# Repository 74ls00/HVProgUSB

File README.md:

# HVProgUSB

Параллельный программатор AVR на базе STK500. Вход на PL2303, для прошивки программатор не требуется

Инструкция по настройке https://74ls00.github.io/hwprog/help.html

2018.10 добавлен светодиод 3.3в PL2303

Фото моего прибора в папке /pic

Вариант в dip корпусе планировался как тестовый, но заброшен

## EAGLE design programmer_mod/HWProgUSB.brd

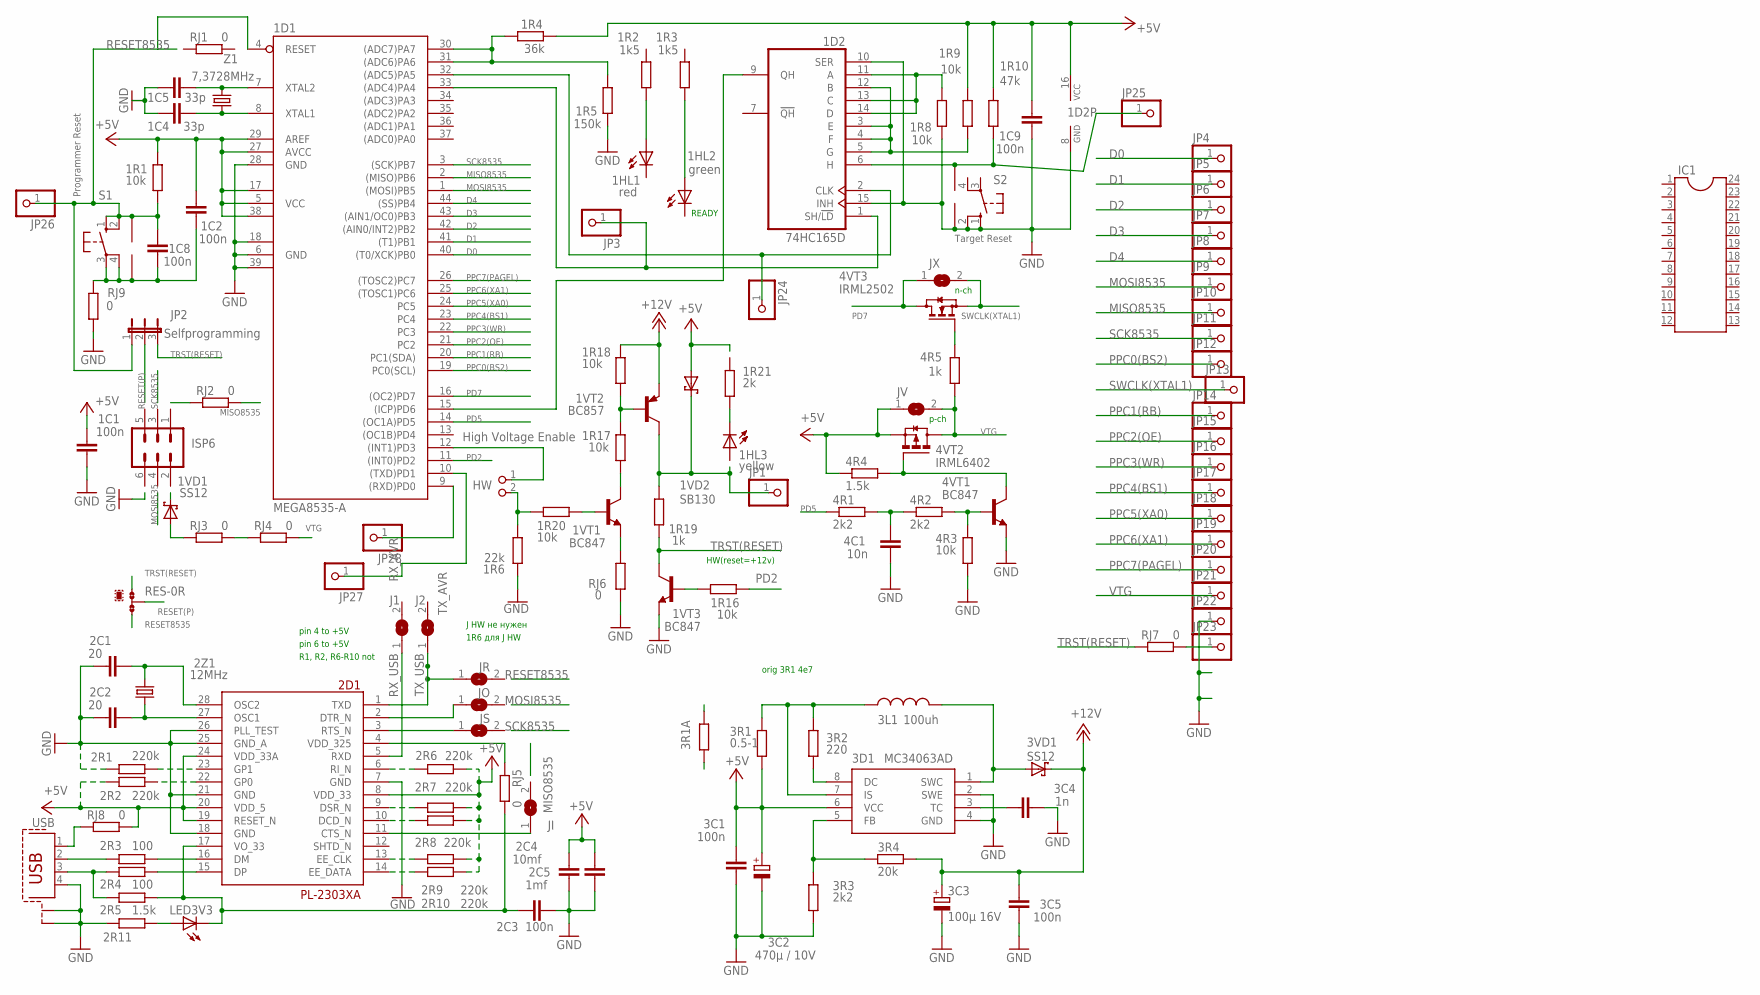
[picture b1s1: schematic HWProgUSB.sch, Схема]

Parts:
1C1, 1C2, 1C8, 1C9, 2C3: 100n; C0805
1C4, 1C5: 33p; C0805
1D1: MEGA8535-A; TQFP44
1D2: 74HC165D; SO16
1HL1: red; LED5MM
1HL2: green; LED5MM
1HL3: yellow; LED5MM
1R1, 1R8, 1R9, 1R17, 1R18, 1R20, 4R3: 10k; M0805
1R2, 1R3: 1k5; M0805
1R4: 36k; M0805
1R5: 150k; R1206
1R6: 22k; M1206
1R10: 47k; M0805
1R16: 10k; R0805
1R19, 4R5: 1k; M0805
1R21: 2k; R1206W
1VD1, 3VD1: SS12; SMB
1VD2: SB130; SMB
1VT1, 1VT3, 4VT1: BC847; SOT23
1VT2: BC857; SOT23-BEC
2C1, 2C2: 20; C0805
2C4: 10mf; C1210
2C5: 1mf; C0805
2D1: PL-2303XA; SSOP28DB
2R1, 2R7, 2R8, 2R9, 2R10: 220k; R0603
2R2, 2R6: 220k; R1206W
2R3, 2R4: 100; R0603
2R5: 1.5k; R0603
2R11: R-EU_R0603; R0603
2Z1: 12MHz; HC49/S
3C1: 100n; C025-024X044
3C2: 470µ / 10V; RCL_E3,5-8
3C3: 100µ 16V; RCL_E3,5-8
3C4: 1n; C025-025X050
3C5: 100n; C025-025X050
3D1: MC34063AD; SOIC8
3L1: 100uh; 0207/10
3R1: 0.5-1; 0204/7
3R1A: R-EU_0204/7; 0204/7
3R2: 220; 0204/7
3R3, 4R1: 2k2; M0805
3R4: 20k; M0805
4C1: 10n; C1206
4R2: 2k2; M1206
4R4: 1.5k; M0805
4VT2: IRML6402; SUPER-SOT3
4VT3: IRML2502; SOT23
HW: High Voltage Enable; PINHEAD_1X02
IC1: DIL24-9
ISP6: MA03-2
J1, J2: SJ
JI: SJ
JO: SJ
JP1, JP3, JP4, JP5, JP6, JP7, JP8, JP9, JP10, JP11, JP12, JP13, JP14, JP15, JP16, JP17, JP18, JP19, JP20, JP21, JP22, JP23, JP24, JP25, JP26, JP27, JP28: PINHD-1X1; 1X01
JP2: Selfprogramming; JUMPER_JP2
JR: SJ
JS: SJ
JV: SJ
JX: SJ
LED3V3: LEDCHIPLED_0603; CHIPLED_0603
RES: 0R-JUMPA; A0R-JMP
RJ1, RJ2, RJ3, RJ4, RJ5, RJ6, RJ7, RJ8, RJ9: 0; R1206
S1, S2: 10-XX; B3F-10XX
U$1, U$2: 5.08; KEY
USB: PROGRAMMER_PN61729-S
Z1: 7,3728MHz; HC49U-V

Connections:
3VUSB: 2C3.1, 2D1.17 (VO_33), 2R5.1, LED3V3.C, RJ5.2
+5V: 1C1.2, 1C2.2, 1C9.1, 1D1.5 (VCC), 1D1.17 (VCC1), 1D1.27 (AVCC), 1D1.29 (AREF), 1D1.38 (VCC2), 1D2.16 (VCC), 1R1.2, 1R4.2, 1R9.1, 1R10.1, 1VD2.A, 2C4.2, 2C5.2, 2D1.8 (VDD_33), 2D1.19 (RESET_N), 2D1.20 (VDD_5), 2D1.24 (VDD_33A), 2R2.1, 2R6.2, 2R7.1, 2R8.1, 2R9.1, 2R10.1, 3C1.1, 3C2.+, 3D1.6 (VCC), 3R1.1, 3R1A.1, 4R4.1, 4VT2.2 (S), JV.1, RJ8.2
+12V: 1R18.2, 1VT2.E, 3C3.+, 3C5.2, 3R4.2, 3VD1.C
D0: 1D1.40 ((T0/XCK)PB0), JP4.1
D1: 1D1.41 ((T1)PB1), JP5.1
D2: 1D1.42 ((AIN0/INT2)PB2), JP6.1
D3: 1D1.43 ((AIN1/OC0)PB3), JP7.1
D4: 1D1.44 ((SS)PB4), JP8.1
GND: 1C1.1, 1C4.1, 1C5.1, 1C9.2, 1D1.6 (GND), 1D1.18 (GND1), 1D1.28 (GND), 1D1.39 (GND2), 1D2.8 (GND), 1D2.10 (SER), 1D2.15 (INH), 1R5.1, 1R6.1, 1R8.1, 1VT3.2 (E), 2C1.1, 2C2.1, 2C3.2, 2C4.1, 2C5.1, 2D1.7 (GND), 2D1.18 (GND), 2D1.21 (GND), 2D1.25 (GND_A), 2D1.26 (PLL_TEST), 2R1.1, 2R11.2, 3C1.2, 3C2.-, 3C3.-, 3C4.2, 3C5.1, 3D1.2 (SWE), 3D1.4 (GND), 3R3.1, 4C1.1, 4R3.1, 4VT1.2 (E), JP22.1, RJ6.1, RJ9.1, S2.1 (S), S2.2 (S1), U$2.P$1, USB.4, USB.S1, USB.S2
MISO8535: 1D1.2 ((MISO)PB6), JP10.1, RJ2.2
MOSI8535: 1D1.1 ((MOSI)PB5), JP9.1
N4: 1D1.33 ((ADC4)PA4), 1D2.1 (SH/!LD), JP3.1
unnamed: JP23.1, RJ7.2
unnamed: 2D1.4 (VDD_325), RJ5.1
unnamed: 1VT1.2 (E), RJ6.2
unnamed: 2D1.9 (DSR_N), 2R7.2
unnamed: 1VD1.A, RJ3.1
unnamed: RJ3.2, RJ4.1
unnamed: 1C5.2, 1D1.7 (XTAL2), Z1.2
unnamed: 1C4.2, 1D1.8 (XTAL1), Z1.1
unnamed: RJ8.1, USB.1
unnamed: 1C2.1, 1C8.1, RJ9.2, S1.3, S1.4 (P1), U$1.P$1
unnamed: 1HL3.K (C), 1R21.1
unnamed: 4R5.2, 4VT3.1 (G)
unnamed: 2R11.1, LED3V3.A
unnamed: 2R4.1, 2R5.2, USB.3
unnamed: 2R3.1, USB.2
unnamed: 2D1.15 (DP), 2R4.2
unnamed: 2D1.16 (DM), 2R3.2
unnamed: 2D1.23 (GP1), 2R1.2
unnamed: 2D1.22 (GP0), 2R2.2
unnamed: 2C1.2, 2D1.28 (OSC2), 2Z1.2
unnamed: 2D1.11 (CTS_N), JI.1
unnamed: 4R2.2, 4R3.2, 4VT1.1 (B)
unnamed: 2C2.2, 2D1.27 (OSC1), 2Z1.1
unnamed: 2D1.6 (RI_N), 2R6.1
unnamed: 4R4.2, 4VT1.3 (C), 4VT2.1 (G)
unnamed: 2D1.3 (RTS_N), JS.1
unnamed: 4C1.2, 4R1.2, 4R2.1
unnamed: 2D1.13 (EE_CLK), 2R9.2
unnamed: 2D1.2 (DTR_N), JO.1
unnamed: 2D1.14 (EE_DATA), 2R10.2
unnamed: 2D1.10 (DCD_N), 2R8.2
unnamed: 3D1.8 (DC), 3R2.1
unnamed: 3D1.7 (IS), 3L1.1, 3R1.2, 3R1A.2, 3R2.2
unnamed: 3D1.5 (FB), 3R3.2, 3R4.1
unnamed: 3D1.1 (SWC), 3L1.2, 3VD1.A
unnamed: 3C4.1, 3D1.3 (TC)
unnamed: 1HL2.A, 1R3.1
unnamed: 1D1.30 ((ADC7)PA7), 1D1.31 ((ADC6)PA6), 1R4.1, 1R5.2
unnamed: 1D1.32 ((ADC5)PA5), 1D2.2 (CLK), JP24.1
unnamed: 1D2.6 (H), 1R10.2, JP25.1, U$2.P$2
unnamed: 1D1.12 ((INT1)PD3), HW.1
unnamed: 1R6.2, 1R20.2, HW.2
unnamed: 1R19.2, 1VD2.C, 1VT2.C, JP1.1
unnamed: 1R20.1, 1VT1.1 (B)
unnamed: 1R17.1, 1VT1.3 (C)
unnamed: 1R17.2, 1R18.1, 1VT2.B
unnamed: 1D1.15 ((ICP)PD6), 1D2.9 (QH)
unnamed: 1HL1.A, 1R2.1
unnamed: 1D2.11 (A), 1D2.13 (C), 1D2.14 (D), 1R8.2
unnamed: 1D2.3 (E), 1D2.4 (F), 1D2.5 (G), 1D2.12 (B), 1R9.2
unnamed: 1R16.2, 1VT3.1 (B)
PD2: 1D1.11 ((INT0)PD2), 1R16.1
PD5: 1D1.14 ((OC1A)PD5), 4R1.1
PD7: 1D1.16 ((OC2)PD7), 4VT3.3 (D), JX.1
PPC0(BS2): 1D1.19 (PC0(SCL)), JP12.1
PPC1(RB): 1D1.20 (PC1(SDA)), JP14.1
PPC2(OE): 1D1.21 (PC2), JP15.1
PPC3(WR): 1D1.22 (PC3), JP16.1
PPC4(BS1): 1D1.23 (PC4), JP17.1
PPC5(XA0): 1D1.24 (PC5), JP18.1
PPC6(XA1): 1D1.25 ((TOSC1)PC6), JP19.1
PPC7(PAGEL): 1D1.26 ((TOSC2)PC7), JP20.1
RESET8535: 1C8.2, 1D1.4 (RESET), 1R1.1, JP2.1, JP26.1, RES.3, S1.1 (S), S1.2 (S1), U$1.P$2
RESET(P): JP2.2, RES.2
RX_AVR: 1D1.10 ((TXD)PD1), JP27.1
RX_USB: 2D1.5 (RXD), J1.1
SCK8535: 1D1.3 ((SCK)PB7), JP11.1
SWCLK(XTAL1): 4VT3.2 (S), JP13.1, JX.2
TRST(RESET): 1R19.1, 1VT3.3 (C), JP2.3, RES.1, RJ7.1
TX_AVR: 1D1.9 ((RXD)PD0), JP28.1
TX_USB: 2D1.1 (TXD), J2.1, JR.1
VTG: 4R5.1, 4VT2.3 (D), JP21.1, JV.2, RJ4.2

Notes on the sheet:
Target Reset
Programmer Reset
pin 4 to +5V
R1, R2, R6-R10 not
pin 6 to +5V
orig 3R1 4e7
J HW не нужен
1R6 для J HW
HW(reset=+12v)
READY
n-ch
p-ch

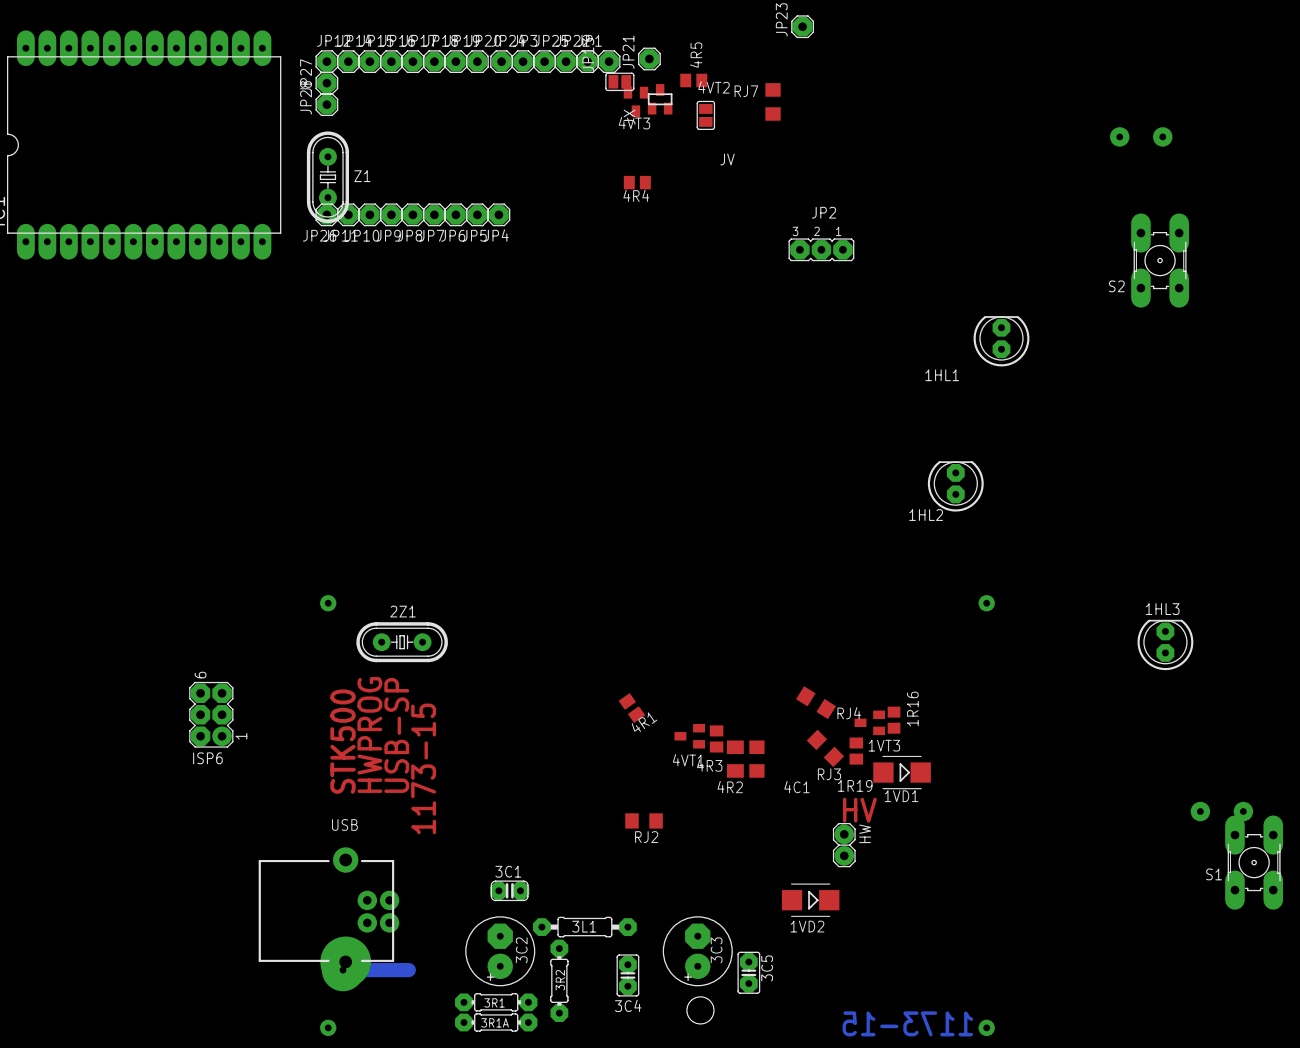
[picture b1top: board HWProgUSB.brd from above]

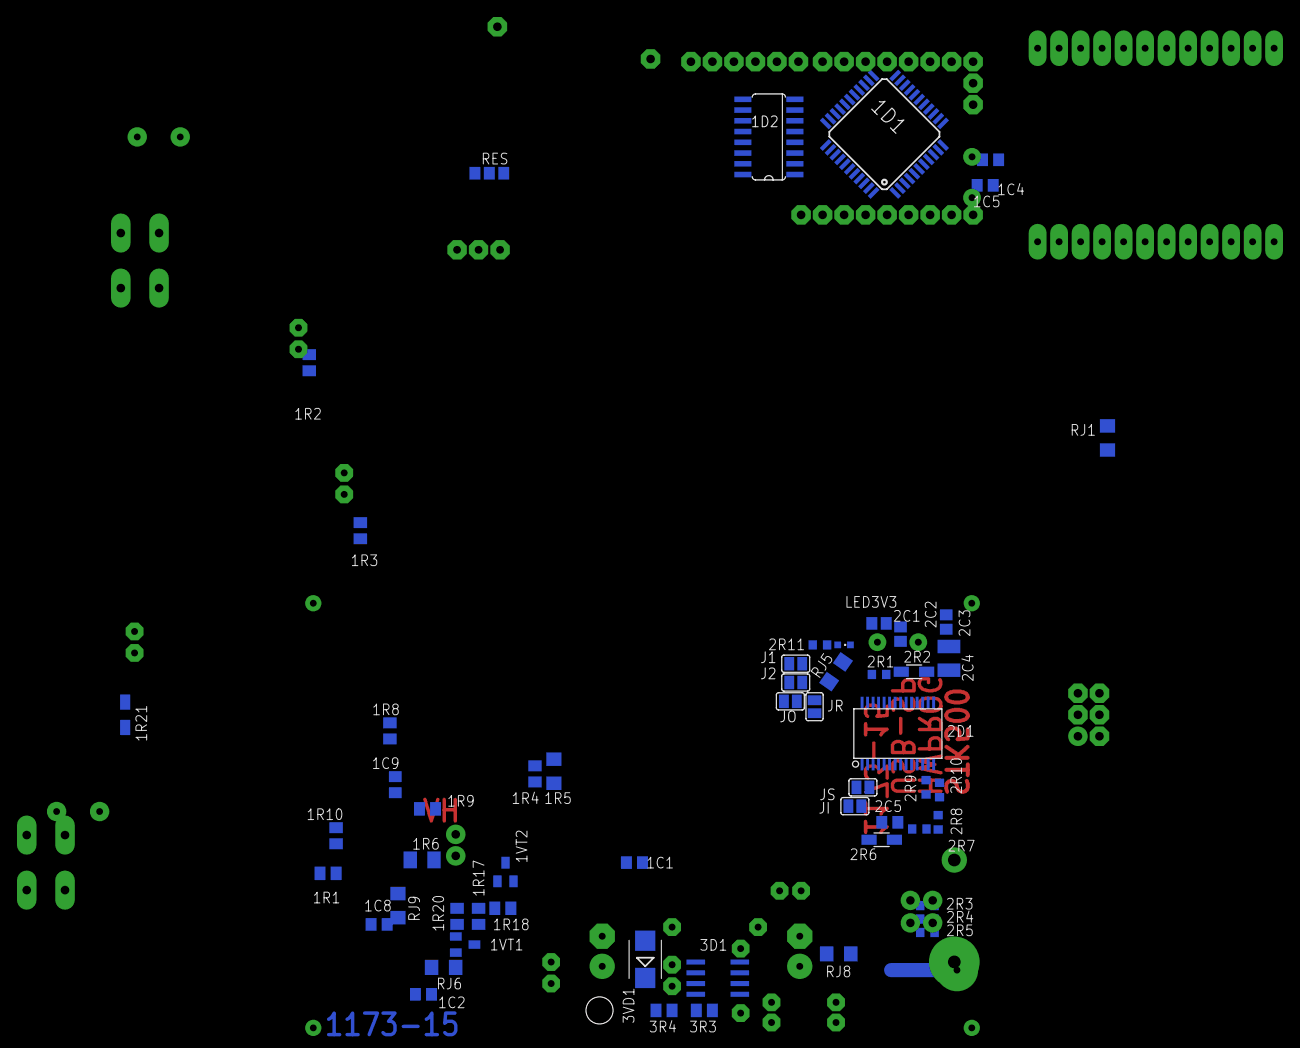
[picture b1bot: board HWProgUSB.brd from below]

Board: 2 copper layers, 127 parts (57 on the bottom side), 84 nets.

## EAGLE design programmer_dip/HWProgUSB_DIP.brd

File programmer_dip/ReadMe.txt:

Эксперементальная плата.
Цель: сборка под DIP компоненты.

Работа не завершена.
Компоненты утеряны, завершение не планируется.

Схема скорее всего завершена.
Плата частично завершена.

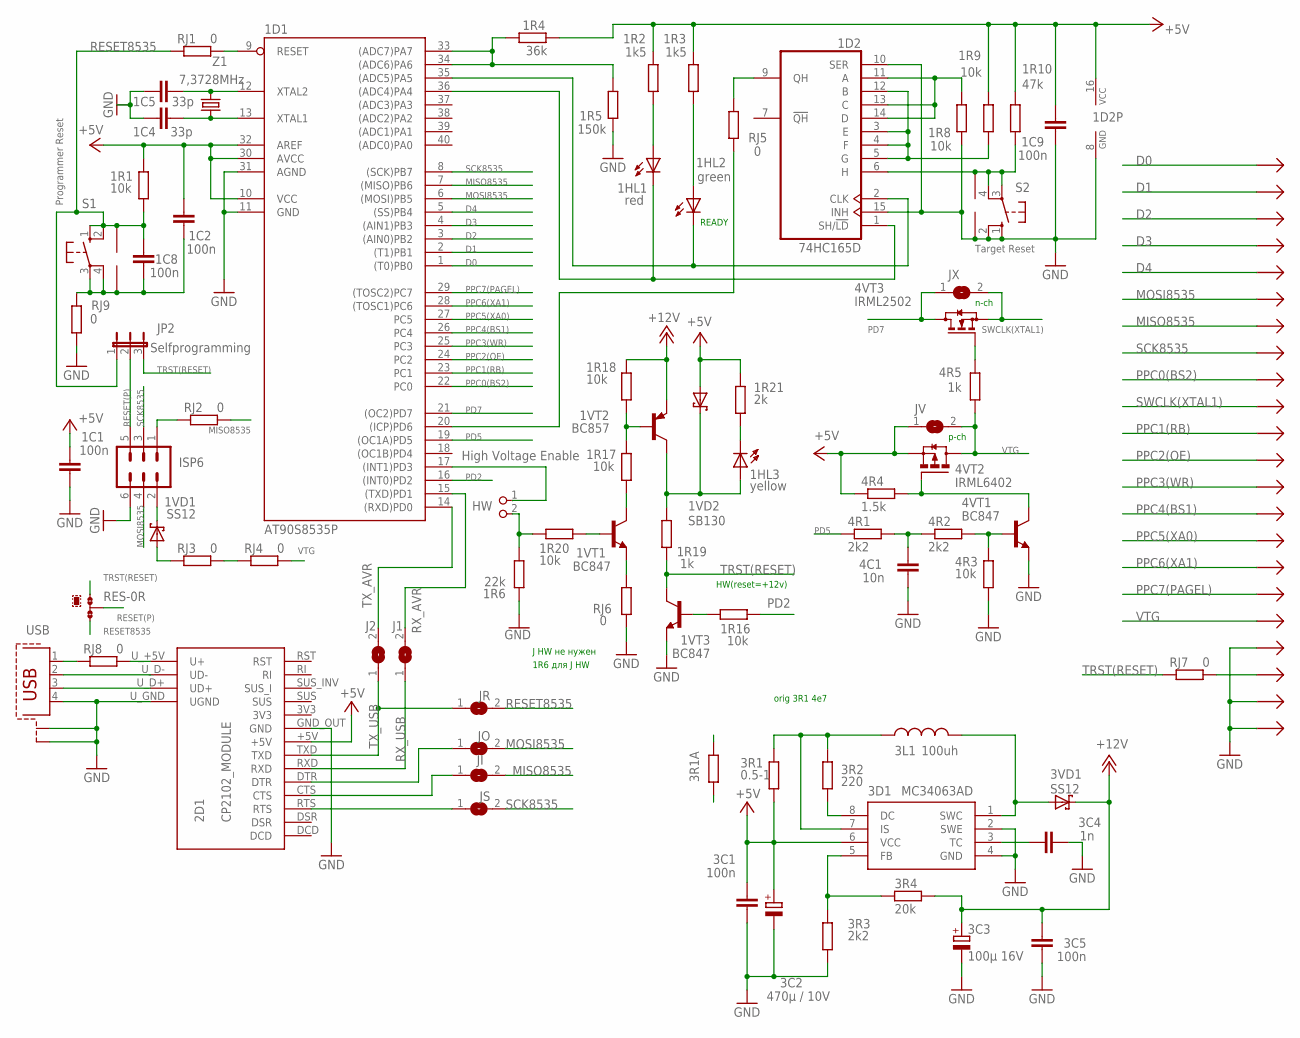
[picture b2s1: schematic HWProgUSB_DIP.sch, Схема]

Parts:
1C1, 1C2, 1C8, 1C9: 100n; C0805
1C4, 1C5: 33p; C0805
1D1: AT90S8535P; DIL40
1D2: 74HC165D; SO16
1HL1: red; LED5MM
1HL2: green; LED5MM
1HL3: yellow; LED5MM
1R1, 1R8, 1R17, 1R18, 1R20, 4R3: 10k; M0805
1R2, 1R3: 1k5; M0805
1R4: 36k; M0805
1R5: 150k; R1206W
1R6: 22k; M1206
1R9: 10k; R1206W
1R10: 47k; M0805
1R16: 10k; R0805
1R19, 4R5: 1k; M0805
1R21: 2k; R1206W
1VD1, 3VD1: SS12; SMB
1VD2: SB130; SMB
1VT1, 1VT3, 4VT1: BC847; SOT23
1VT2: BC857; SOT23-BEC
2D1: CP2102_MODULE
3C1: 100n; C025-024X044
3C2: 470µ / 10V; RCL_E3,5-8
3C3: 100µ 16V; RCL_E3,5-8
3C4: 1n; C025-025X050
3C5: 100n; C025-025X050
3D1: MC34063AD; SOIC8
3L1: 100uh; 0207/10
3R1: 0.5-1; 0204/7
3R1A: R-EU_0204/7; 0204/7
3R2: 220; 0204/7
3R3, 4R2: 2k2; M0805
3R4: 20k; M0805
4C1: 10n; C1206
4R1: 2k2; R1206W
4R4: 1.5k; M0805
4VT2: IRML6402; SUPER-SOT3
4VT3: IRML2502; SOT23
HW: High Voltage Enable; PINHEAD_1X02
ISP6: MA03-2
J1, J2: SJ
JI: SJ
JO: SJ
JP2: Selfprogramming; JUMPER_JP2
JR: SJ
JS: SJ
JV: SJ
JX: SJ
RES: 0R-JUMPA; A0R-JMP
RJ1, RJ2, RJ3, RJ4, RJ6, RJ7, RJ8, RJ9: 0; R1206
RJ5: 0; R1206W
S1, S2: 10-XX; B3F-10XX
U$1, U$2: 5.08; KEY
USB: PROGRAMMER_PN61729-S
X2: P_AVR_V; CON-PCI
Z1: 7,3728MHz; HC49U-V

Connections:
+5V: 1C1.2, 1C2.2, 1C9.1, 1D1.10 (VCC), 1D1.30 (AVCC), 1D1.32 (AREF), 1D2.16 (VCC), 1R1.2, 1R2.2, 1R3.2, 1R4.2, 1R9.1, 1R10.1, 1R21.2, 1VD2.A, 2D1.+5V, 3C1.1, 3C2.+, 3D1.6 (VCC), 3R1.1, 3R1A.1, 4R4.1, 4VT2.2 (S), JV.1
+12V: 1R18.2, 1VT2.E, 3C3.+, 3C5.2, 3R4.2, 3VD1.C
D0: 1D1.1 ((T0)PB0), X2.1D0 (D0), X2.2D0 (D0)
D1: 1D1.2 ((T1)PB1), X2.1D1 (D1), X2.2D1 (D1)
D2: 1D1.3 ((AIN0)PB2), X2.1D2 (D2), X2.2D2 (D2)
D3: 1D1.4 ((AIN1)PB3), X2.1D3 (D3), X2.2D3 (D3)
D4: 1D1.5 ((SS)PB4), X2.1D4 (D4), X2.2D4 (D4)
GND: 1C1.1, 1C4.1, 1C5.1, 1C9.2, 1D1.11 (GND), 1D1.31 (AGND), 1D2.8 (GND), 1D2.10 (SER), 1D2.15 (INH), 1R5.1, 1R6.1, 1R8.1, 1VT3.2 (E), 2D1.GND_OUT (GND), 2D1.U_GND (UGND), 3C1.2, 3C2.-, 3C3.-, 3C4.2, 3C5.1, 3D1.2 (SWE), 3D1.4 (GND), 3R3.1, 4C1.1, 4R3.1, 4VT1.2 (E), ISP6.6, RJ6.1, RJ9.1, S2.1 (S), S2.2 (S1), U$2.P$1, USB.4, USB.S1, USB.S2, X2.0 (GND), X2.1 (GND), X2.1GND1 (GND2), X2.1GND2 (LGND), X2.2 (GND), X2.2GND1 (GND2), X2.2GND2 (LGND), X2.3 (GND), X2.4 (GND), X2.5 (GND), X2.6 (GND), X2.7 (GND), X2.8 (GND), X2.9 (GND), X2.10 (GND), X2.11 (GND), X2.12 (GND), X2.13 (GND), X2.14 (GND), X2.15 (GND), X2.16 (GND), X2.17 (GND), X2.18 (GND), X2.19 (GND), X2.20 (GND), X2.21 (GND), X2.22 (GND), X2.23 (GND), X2.24 (GND), X2.25 (GND), X2.26 (GND), X2.27 (GND), X2.28 (GND), X2.29 (GND), X2.30 (GND), X2.31 (GND), X2.32 (GND), X2.33 (GND), X2.34 (GND), X2.35 (GND), X2.36 (GND), X2.37 (GND), X2.38 (GND), X2.39 (GND), X2.40 (GND)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
MISO8535: 1D1.7 ((MISO)PB6), JI.2, RJ2.2, X2.1D6 (D6), X2.2D6 (D6)
MOSI8535: 1D1.6 ((MOSI)PB5), ISP6.4, JO.2, X2.1D5 (D5), X2.2D5 (D5)
N4: 1D1.36 ((ADC4)PA4), 1D2.1 (SH/!LD), 1HL1.K (C)
unnamed: RJ7.2, X2.1RESET (RESET), X2.2RESET (RESET)
unnamed: 1D1.9 (RESET), RJ1.2
unnamed: ISP6.1, RJ2.1
unnamed: 2D1.U_+5V (U+), RJ8.2
unnamed: 1VT1.2 (E), RJ6.2
unnamed: 1VD1.C, ISP6.2
unnamed: 2D1.CTS, JI.1
unnamed: 1VD1.A, RJ3.1
unnamed: RJ3.2, RJ4.1
unnamed: 1C5.2, 1D1.12 (XTAL2), Z1.2
unnamed: 1C4.2, 1D1.13 (XTAL1), Z1.1
unnamed: RJ8.1, USB.1
unnamed: 1C2.1, 1C8.1, RJ9.2, S1.3, S1.4 (P1), U$1.P$1
unnamed: 1HL3.K (C), 1R21.1
unnamed: 4R5.2, 4VT3.1 (G)
unnamed: 1D2.9 (QH), RJ5.2
unnamed: 2D1.U_D+ (UD+), USB.3
unnamed: 2D1.U_D- (UD-), USB.2
unnamed: 4R2.2, 4R3.2, 4VT1.1 (B)
unnamed: 4R4.2, 4VT1.3 (C), 4VT2.1 (G)
unnamed: 2D1.RTS, JS.1
unnamed: 4C1.2, 4R1.2, 4R2.1
unnamed: 2D1.DTR, JO.1
unnamed: 3D1.8 (DC), 3R2.1
unnamed: 3D1.7 (IS), 3L1.1, 3R1.2, 3R1A.2, 3R2.2
unnamed: 3D1.5 (FB), 3R3.2, 3R4.1
unnamed: 3D1.1 (SWC), 3L1.2, 3VD1.A
unnamed: 3C4.1, 3D1.3 (TC)
unnamed: 1HL2.A, 1R3.1
unnamed: 1D1.33 ((ADC7)PA7), 1D1.34 ((ADC6)PA6), 1R4.1, 1R5.2
unnamed: 1D1.35 ((ADC5)PA5), 1D2.2 (CLK), 1HL2.K (C)
unnamed: 1D2.6 (H), 1R10.2, S2.3, S2.4 (P1), U$2.P$2
unnamed: 1D1.17 ((INT1)PD3), HW.1
unnamed: 1R6.2, 1R20.2, HW.2
unnamed: 1HL3.A, 1R19.2, 1VD2.C, 1VT2.C
unnamed: 1R20.1, 1VT1.1 (B)
unnamed: 1R17.1, 1VT1.3 (C)
unnamed: 1R17.2, 1R18.1, 1VT2.B
unnamed: 1D1.20 ((ICP)PD6), RJ5.1
unnamed: 1HL1.A, 1R2.1
unnamed: 1D2.11 (A), 1D2.13 (C), 1D2.14 (D), 1R8.2
unnamed: 1D2.3 (E), 1D2.4 (F), 1D2.5 (G), 1D2.12 (B), 1R9.2
unnamed: 1R16.2, 1VT3.1 (B)
PD2: 1D1.16 ((INT0)PD2), 1R16.1
PD5: 1D1.19 ((OC1A)PD5), 4R1.1
PD7: 1D1.21 ((OC2)PD7), 4VT3.3 (D), JX.1
PPC0(BS2): 1D1.22 (PC0), X2.1BS2 (BS2), X2.2BS2 (BS2)
PPC1(RB): 1D1.23 (PC1), X2.1RB (RB), X2.2RB (RB)
PPC2(OE): 1D1.24 (PC2), X2.1OE (OE), X2.2OE (OE)
PPC3(WR): 1D1.25 (PC3), X2.1WR (WR), X2.2WR (WR)
PPC4(BS1): 1D1.26 (PC4), X2.1BS1 (BS1), X2.2BS1 (BS1)
PPC5(XA0): 1D1.27 (PC5), X2.1XA0 (XA0), X2.2XA0 (XA0)
PPC6(XA1): 1D1.28 ((TOSC1)PC6), X2.1XA1 (XA1), X2.2XA1 (XA1)
PPC7(PAGEL): 1D1.29 ((TOSC2)PC7), X2.1PAGEL (PAGEL), X2.2PAGEL (PAGEL)
RESET8535: 1C8.2, 1R1.1, JP2.1, JR.2, RES.3, RJ1.1, S1.1 (S), S1.2 (S1), U$1.P$2
RESET(P): ISP6.5, JP2.2, RES.2
RX_AVR: 1D1.15 ((TXD)PD1), J1.2
RX_USB: 2D1.RXD, J1.1
SCK8535: 1D1.8 ((SCK)PB7), ISP6.3, JS.2, X2.1D7 (D7), X2.2D7 (D7)
SWCLK(XTAL1): 4VT3.2 (S), JX.2, X2.1XTAL1 (XTAL1), X2.2XTAL1 (XTAL1)
TRST(RESET): 1R19.1, 1VT3.3 (C), JP2.3, RES.1, RJ7.1
TX_AVR: 1D1.14 ((RXD)PD0), J2.2
TX_USB: 2D1.TXD, J2.1, JR.1
VTG: 4R5.1, 4VT2.3 (D), JV.2, RJ4.2, X2.1VCC1 (VCC), X2.2VCC1 (VCC)

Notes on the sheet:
Target Reset
Programmer Reset
orig 3R1 4e7
J HW не нужен
1R6 для J HW
HW(reset=+12v)
READY
n-ch
p-ch

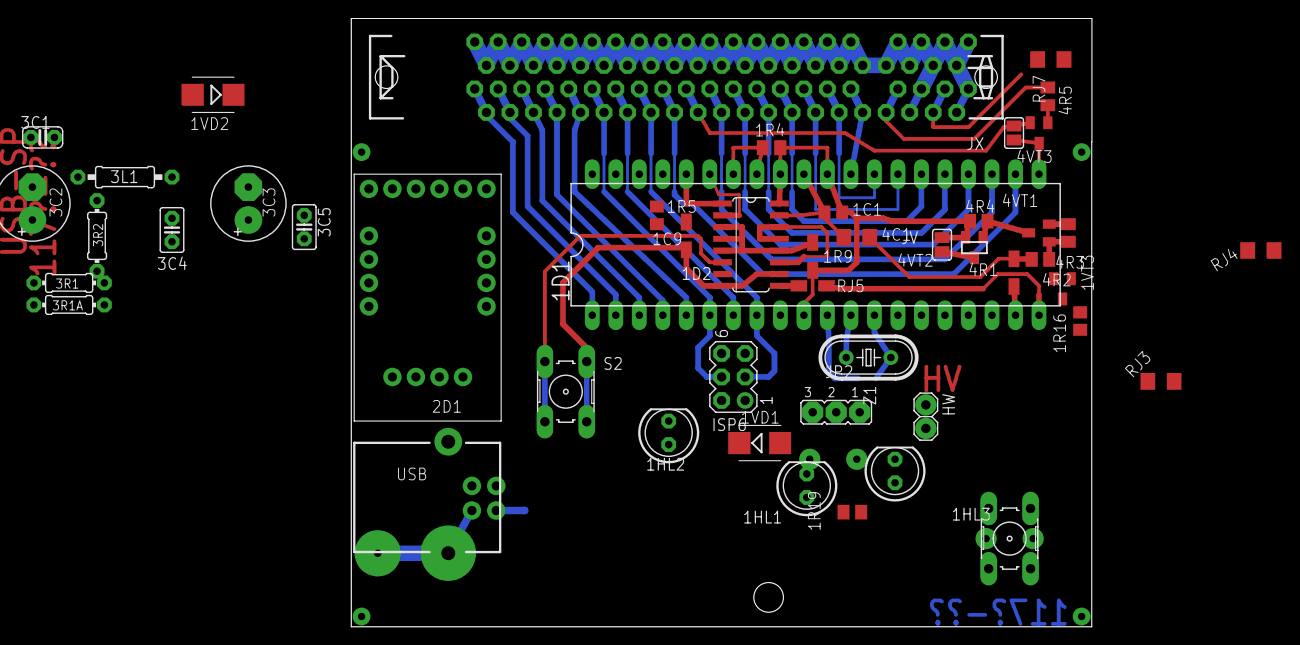
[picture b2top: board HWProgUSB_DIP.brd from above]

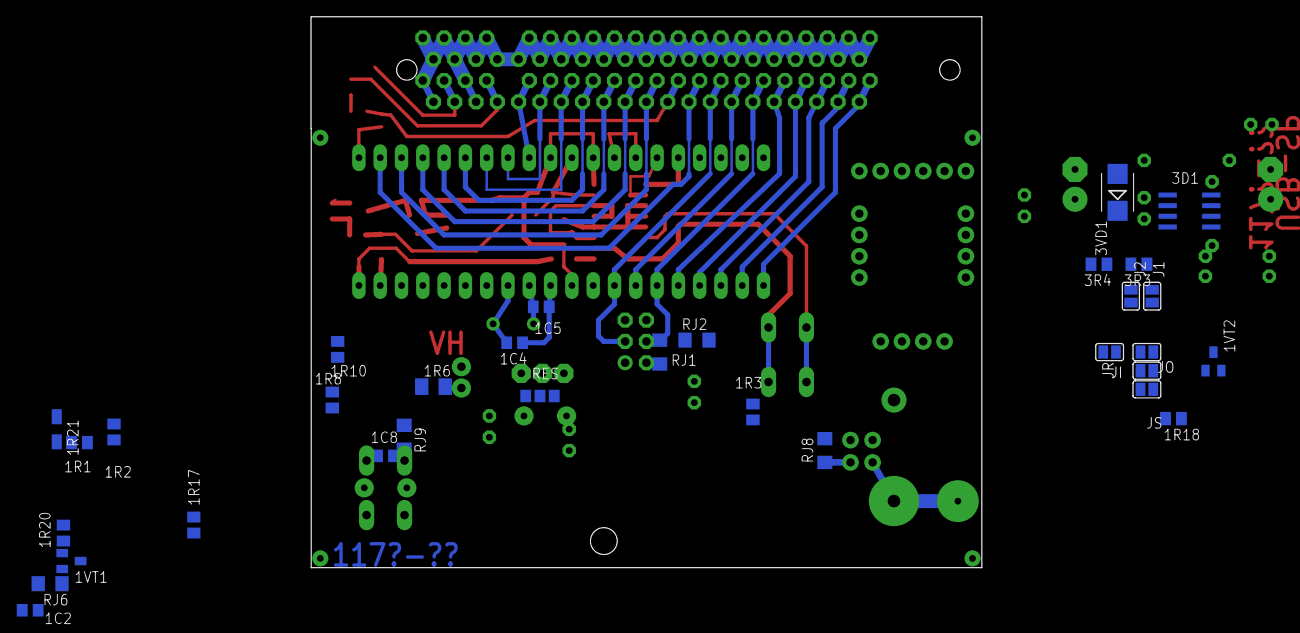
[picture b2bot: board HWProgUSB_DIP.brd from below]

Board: 2 copper layers, 80.0 x 65.7 mm, 82 parts (32 on the bottom side), 75 nets.

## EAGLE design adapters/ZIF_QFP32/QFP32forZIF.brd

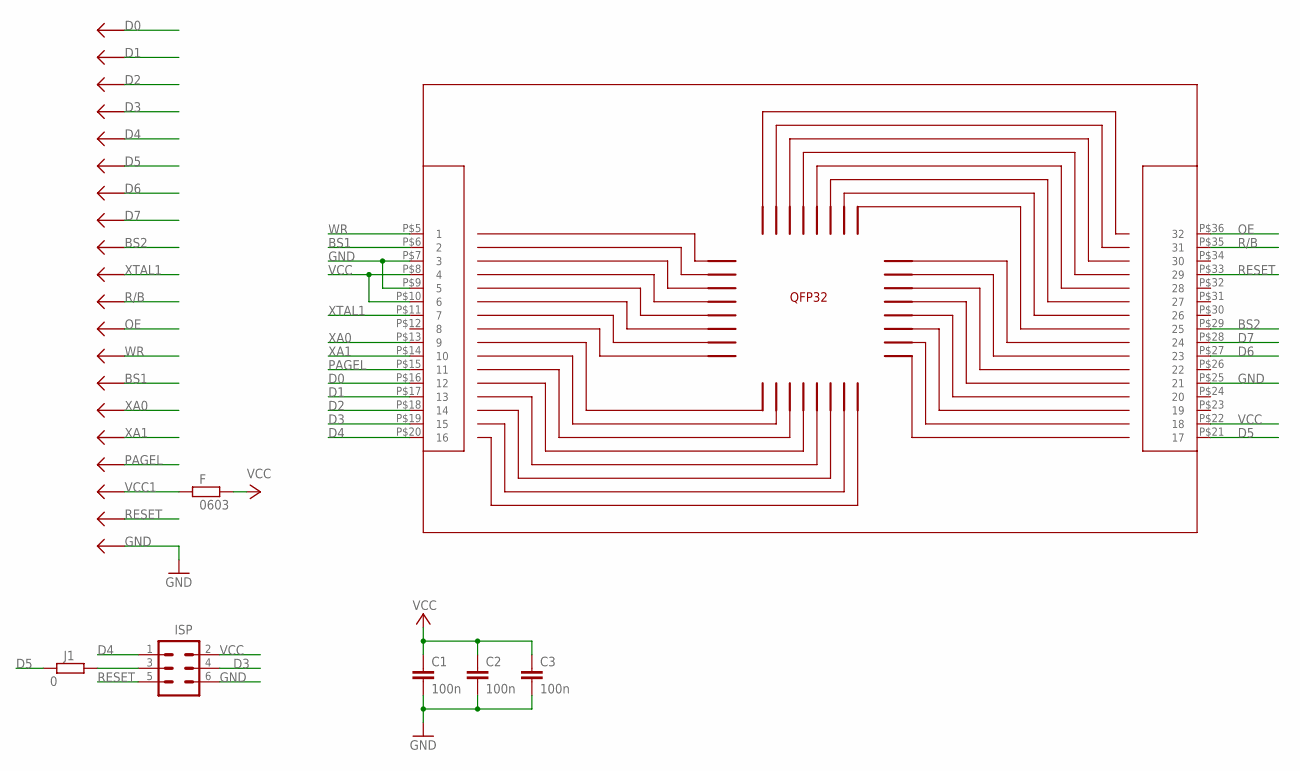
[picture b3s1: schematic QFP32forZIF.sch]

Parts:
C1, C2, C3: 100n; RCL_C0805
F: 0603; RCL_M0805
ISP: MA03-2
J1: 0; R1206W
U$1: PROGRAMMER_P_AVR
U$14: SA636-40; ADAPTERQFP48FORZIF

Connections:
BS1: U$1.BS1, U$14.P$6 (2)
BS2: U$1.BS2, U$14.P$29 (25)
D0: U$1.D0, U$14.P$16 (12)
D1: U$1.D1, U$14.P$17 (13)
D2: U$1.D2, U$14.P$18 (14)
D3: ISP.4, U$1.D3, U$14.P$19 (15)
D4: ISP.1, U$1.D4, U$14.P$20 (16)
D5: J1.1, U$1.D5, U$14.P$21 (17)
D6: U$1.D6, U$14.P$27 (23)
D7: U$1.D7, U$14.P$28 (24)
GND: C1.2, C2.2, C3.2, ISP.6, U$1.GND, U$1.GND01 (GND), U$1.GND2 (GND), U$1.GND03 (GND), U$1.GND04 (GND), U$1.GND05 (GND), U$1.GND06 (GND), U$1.GND07 (GND), U$1.GND08 (GND), U$1.GND09 (GND), U$1.GND10 (GND), U$1.GND11 (GND), U$1.GND12 (GND), U$1.GND13 (GND), U$1.GND14 (GND), U$1.GND15 (GND), U$1.GND16 (GND), U$1.GND17 (GND), U$1.GND18 (GND), U$1.GND19 (GND), U$1.GND20 (GND), U$1.GND21 (GND), U$1.GND22 (GND), U$14.P$7 (3), U$14.P$9 (5), U$14.P$25 (21)
unnamed: ISP.3, J1.2
OE: U$1.OE, U$14.P$36 (32)
PAGEL: U$1.PAGEL, U$14.P$15 (11)
R/B: U$1.RB, U$14.P$35 (31)
RESET: ISP.5, U$1.RESET, U$14.P$33 (29)
VCC: C1.1, C2.1, C3.1, F.2, ISP.2, U$14.P$8 (4), U$14.P$10 (6), U$14.P$22 (18)
VCC1: F.1, U$1.VCC
WR: U$1.WR, U$14.P$5 (1)
XA0: U$1.XA0, U$14.P$13 (9)
XA1: U$1.XA1, U$14.P$14 (10)
XTAL1: U$1.XTAL1, U$14.P$11 (7)

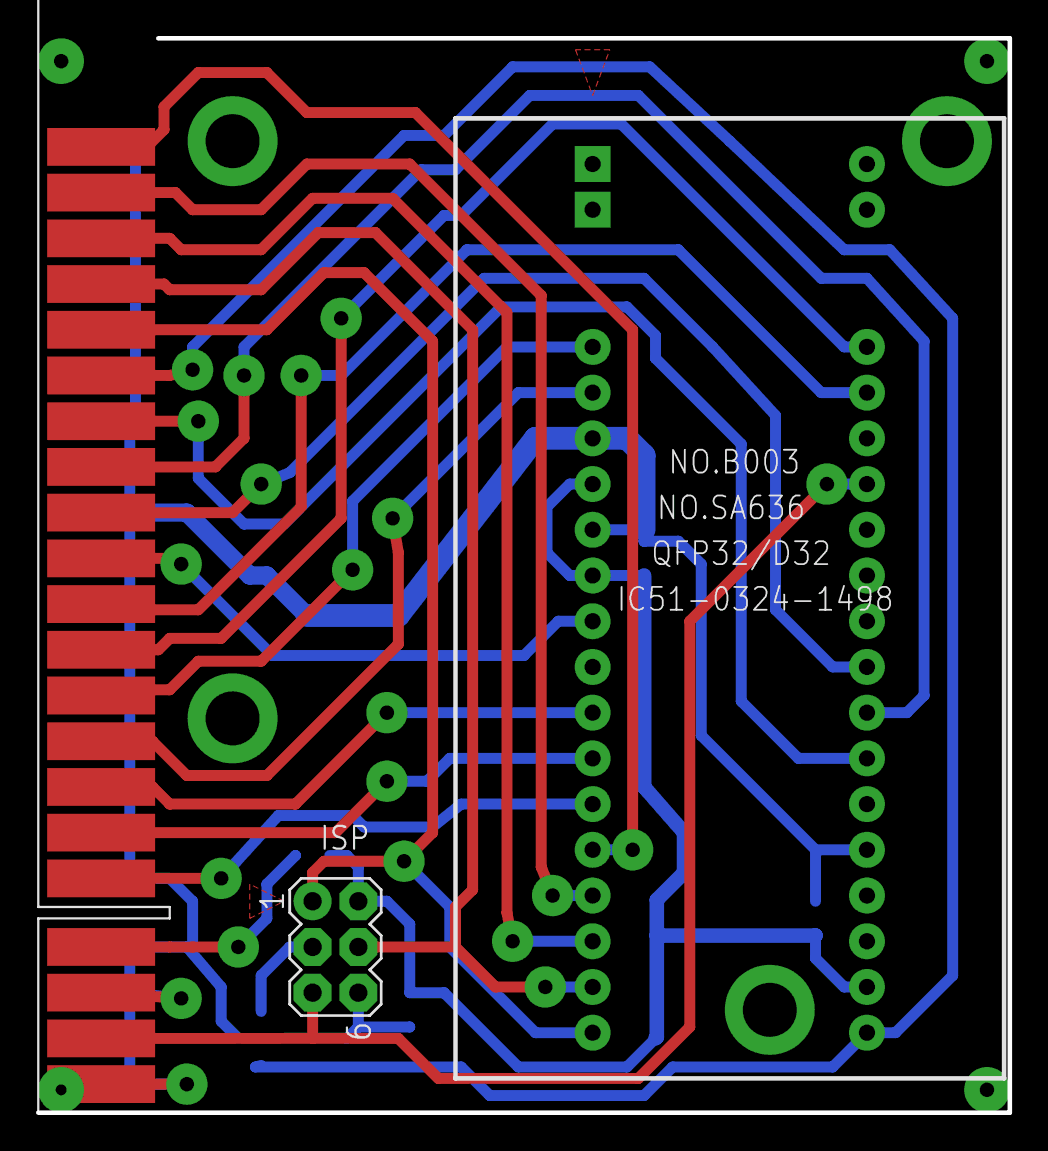
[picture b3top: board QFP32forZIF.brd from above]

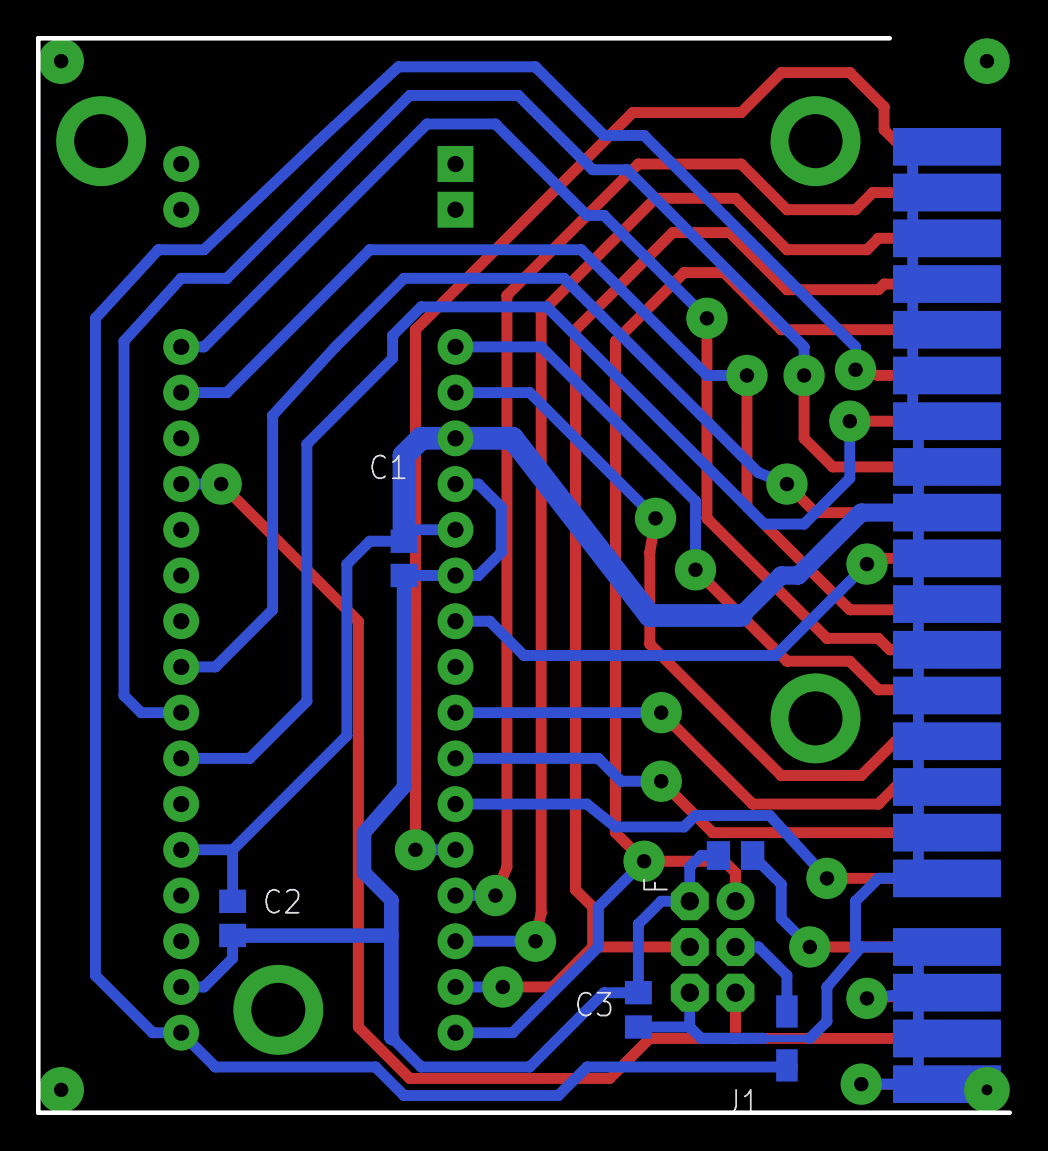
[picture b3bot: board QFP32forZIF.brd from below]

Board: 2 copper layers, 54.0 x 59.7 mm, 8 parts (5 on the bottom side), 22 nets.

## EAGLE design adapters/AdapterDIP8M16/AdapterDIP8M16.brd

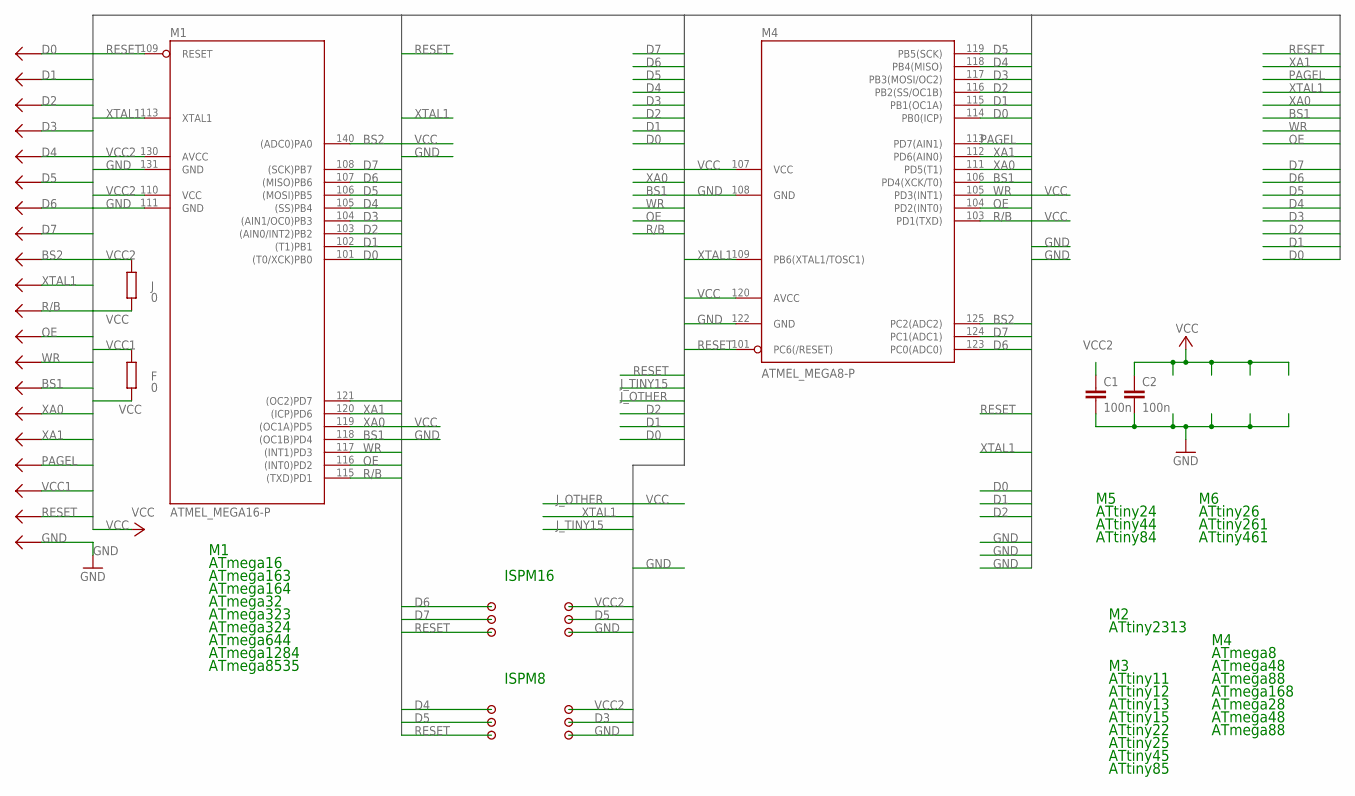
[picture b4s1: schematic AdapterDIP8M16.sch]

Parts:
C1, C2: 100n; RCL_C0805
F: 0; RCL_M0805
J: 0; RCL_M1206
M1: ATMEL_MEGA16-P; ATMEL_DIL40
M4: ATMEL_MEGA8-P; ATMEL_DIL28-3
U$1: PROGRAMMER_P_AVR
U$2, U$3, U$4, U$5, U$6, U$7, U$8, U$9, U$10, U$11, U$12, U$13: PIN

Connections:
BS1: M1.118 ((OC1B)PD4), M4.106 (PD4(XCK/T0)), U$1.BS1
BS2: M1.140 ((ADC0)PA0), M4.125 (PC2(ADC2)), U$1.BS2
D0: M1.101 ((T0/XCK)PB0), M4.114 (PB0(ICP)), U$1.D0
D1: M1.102 ((T1)PB1), M4.115 (PB1(OC1A)), U$1.D1
D2: M1.103 ((AIN0/INT2)PB2), M4.116 (PB2(SS/OC1B)), U$1.D2
D3: M1.104 ((AIN1/OC0)PB3), M4.117 (PB3(MOSI/OC2)), U$1.D3, U$12.P$1
D4: M1.105 ((SS)PB4), M4.118 (PB4(MISO)), U$1.D4, U$8.P$1
D5: M1.106 ((MOSI)PB5), M4.119 (PB5(SCK)), U$1.D5, U$3.P$1, U$9.P$1
D6: M1.107 ((MISO)PB6), M4.123 (PC0(ADC0)), U$1.D6, U$5.P$1
D7: M1.108 ((SCK)PB7), M4.124 (PC1(ADC1)), U$1.D7, U$6.P$1
GND: C1.2, C2.2, M1.111 (GND), M1.131 (GND), M4.108 (GND), M4.122 (GND), U$1.GND, U$1.GND01 (GND), U$1.GND2 (GND), U$1.GND03 (GND), U$1.GND04 (GND), U$1.GND05 (GND), U$1.GND06 (GND), U$1.GND07 (GND), U$1.GND08 (GND), U$1.GND09 (GND), U$1.GND10 (GND), U$1.GND11 (GND), U$1.GND12 (GND), U$1.GND13 (GND), U$1.GND14 (GND), U$1.GND15 (GND), U$1.GND16 (GND), U$1.GND17 (GND), U$1.GND18 (GND), U$1.GND19 (GND), U$1.GND20 (GND), U$1.GND21 (GND), U$1.GND22 (GND), U$4.P$1, U$11.P$1
OE: M1.116 ((INT0)PD2), M4.104 (PD2(INT0)), U$1.OE
PAGEL: M1.121 ((OC2)PD7), M4.113 (PD7(AIN1)), U$1.PAGEL
R/B: M1.115 ((TXD)PD1), M4.103 (PD1(TXD)), U$1.RB
RESET: M1.109 (RESET), M4.101 (PC6(/RESET)), U$1.RESET, U$7.P$1, U$10.P$1
VCC: C2.1, F.2, J.2, M4.107 (VCC), M4.120 (AVCC)
VCC1: F.1, U$1.VCC
VCC2: C1.1, J.1, M1.110 (VCC), M1.130 (AVCC), U$2.P$1, U$13.P$1
WR: M1.117 ((INT1)PD3), M4.105 (PD3(INT1)), U$1.WR
XA0: M1.119 ((OC1A)PD5), M4.111 (PD5(T1)), U$1.XA0
XA1: M1.120 ((ICP)PD6), M4.112 (PD6(AIN0)), U$1.XA1
XTAL1: M1.113 (XTAL1), M4.109 (PB6(XTAL1/TOSC1)), U$1.XTAL1

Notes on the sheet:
ATmega16
ATmega163
ATmega164
ATmega32
ATmega323
ATmega324
ATmega644
ATmega1284
ATmega8535
ATtiny2313
ATtiny11
ATtiny12
ATtiny13
ATtiny15
ATtiny22
ATtiny25
ATtiny45
ATtiny85
ATmega8
ATmega48
ATmega88
ATmega168
ATmega28
ATtiny24
ATtiny44
ATtiny84
ATtiny26
ATtiny261
ATtiny461
ISPM16
ISPM8

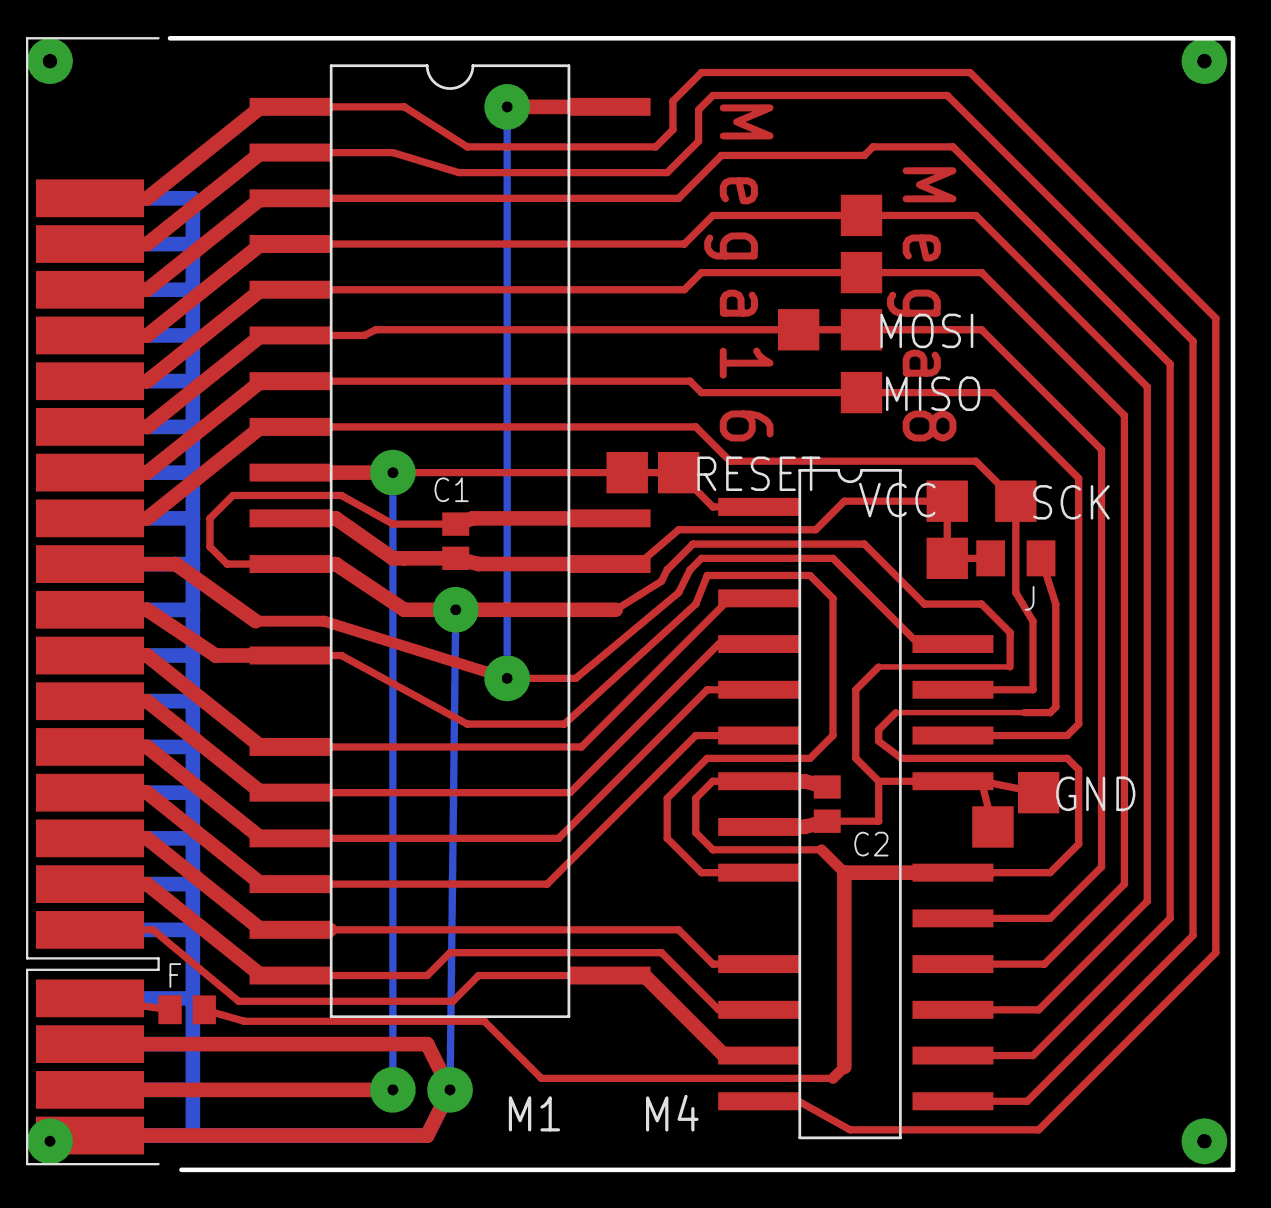
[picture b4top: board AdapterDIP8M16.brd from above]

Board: 2 copper layers, 59.1 x 62.9 mm, 19 parts (0 on the bottom side), 22 nets.

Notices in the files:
parts and their libraries:
SparkFun-DigitalIC: Licensing: Creative Commons ShareAlike 4.0 International - https://creativecommons.org/licenses/by-sa/4.0
